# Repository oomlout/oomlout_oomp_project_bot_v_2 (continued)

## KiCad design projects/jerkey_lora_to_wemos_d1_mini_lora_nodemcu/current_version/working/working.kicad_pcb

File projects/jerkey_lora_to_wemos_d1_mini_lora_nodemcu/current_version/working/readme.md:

# lora_to_wemos_d1_mini
 
## summary 
* id: jerkey_lora_to_wemos_d1_mini_lora_nodemcu
* user: jerkey
* name: lora_to_wemos_d1_mini
* board: lora_nodemcu
* repo: https://github.com/jerkey/Lora-to-Wemos-D1-mini
* src_file_repo_kicad_pcb: lora_nodemcu.kicad_pcb
* src_file_repo_kicad_pcb_link: https://github.com/jerkey/Lora-to-Wemos-D1-mini/tree/master/lora_nodemcu.kicad_pcb

* src_file_repo_sch: lora_nodemcu.sch
* src_file_repo_sch_link: https://github.com/jerkey/Lora-to-Wemos-D1-mini/tree/master/lora_nodemcu.sch
* full details link: https://github.com/oomlout/oomlout_oomp_project_bot_v_2/tree/main/projects/jerkey_lora_to_wemos_d1_mini_lora_nodemcu/current_version/working

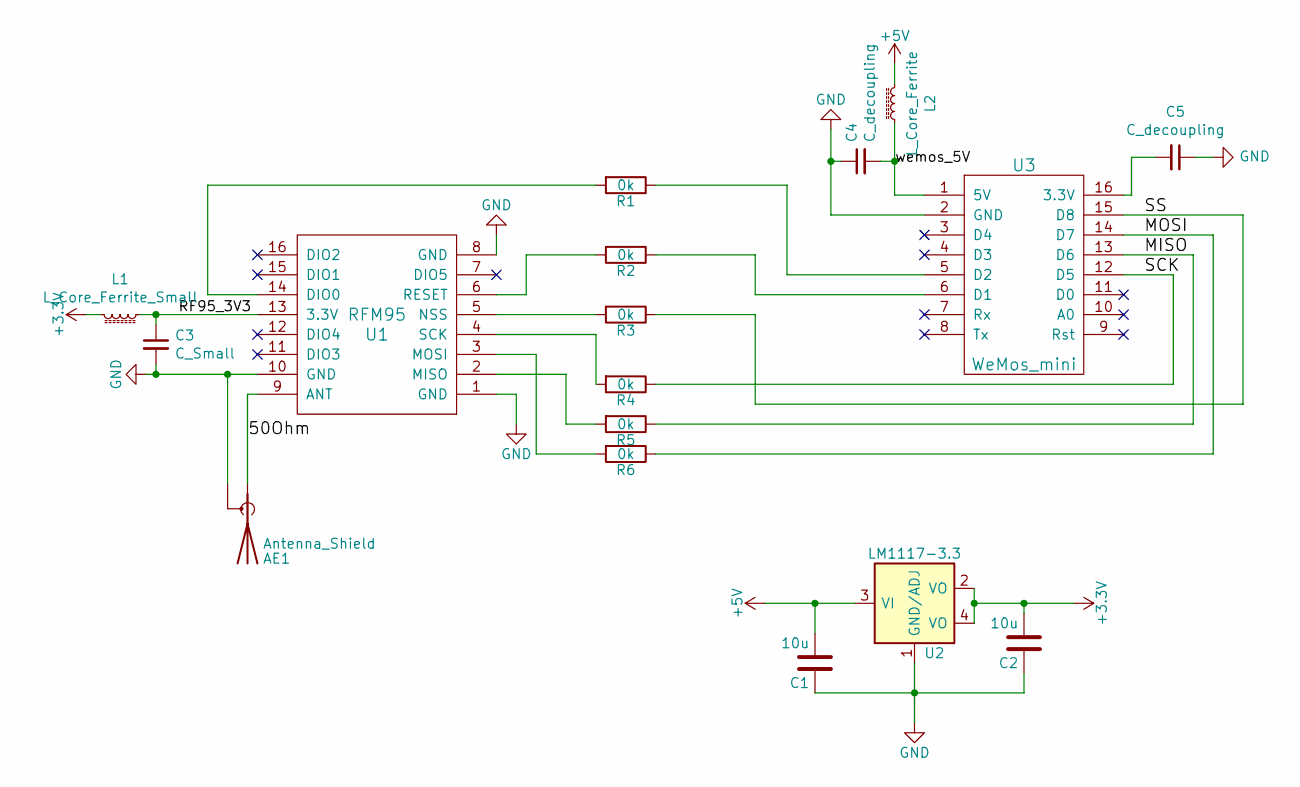
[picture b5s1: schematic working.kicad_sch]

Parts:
AE1: Antenna_Shield; Molex_SMA_Jack_Edge_Mount
C1, C2: 10u; C_0805_HandSoldering
C3: C_Small; C_0805_HandSoldering
C4, C5: C_decoupling; C_0805_HandSoldering
L1: L_Core_Ferrite_Small; L_0805_HandSoldering
L2: L_Core_Ferrite; L_0805_HandSoldering
R1, R2, R3, R4, R5, R6: 0k; R_0805_HandSoldering
U1: RFM95
U2: LM1117-3.3; SOT-223
U3: WeMos_mini; D1_mini_board

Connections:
+3V3: C2.2, L1.2, U2.2 (VO), U2.4 (VO)
+5V: C1.2, L2.2, U2.3 (VI)
/50Ohm: AE1.1 (A), U1.9 (ANT)
/MISO: R5.1, U3.13 (D6)
/MOSI: R6.1, U3.14 (D7)
/RF95_3V3: C3.1, L1.1, U1.13 (3.3V)
/SCK: R4.1, U3.12 (D5)
/SS: R3.1, U3.15 (D8)
/wemos_5V: C4.2, L2.1, U3.1 (5V)
GND: AE1.2 (Shield), C1.1, C2.1, C3.2, C4.1, C5.1, U1.1 (GND), U1.8 (GND), U1.10 (GND), U2.1 (GND/ADJ), U3.2 (GND)
unnamed: C5.2, U3.16 (3.3V)
unnamed: R1.1, U3.5 (D2)
unnamed: R1.2, U1.14 (DIO0)
unnamed: R2.1, U3.6 (D1)
unnamed: R2.2, U1.6 (RESET)
unnamed: R3.2, U1.5 (NSS)
unnamed: R4.2, U1.4 (SCK)
unnamed: R5.2, U1.2 (MISO)
unnamed: R6.2, U1.3 (MOSI)

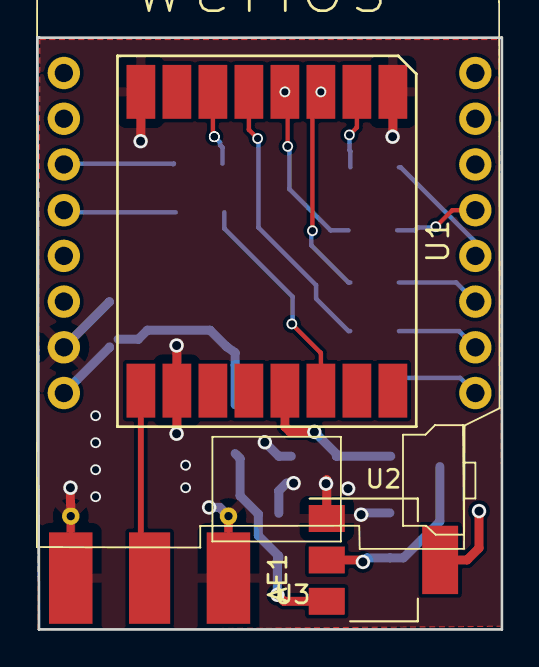
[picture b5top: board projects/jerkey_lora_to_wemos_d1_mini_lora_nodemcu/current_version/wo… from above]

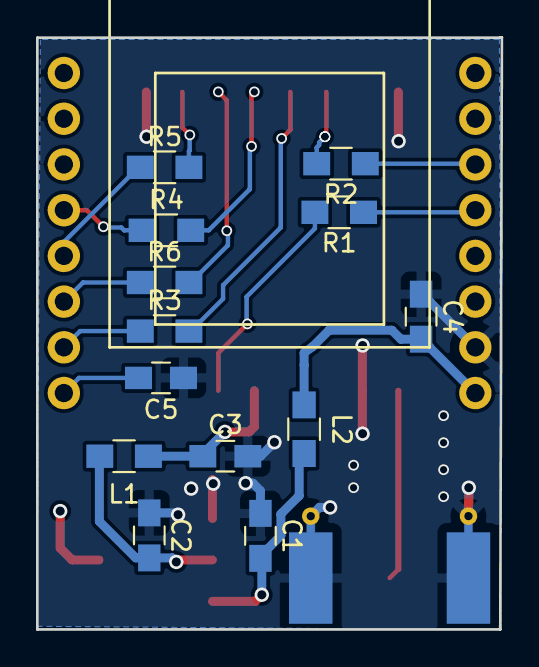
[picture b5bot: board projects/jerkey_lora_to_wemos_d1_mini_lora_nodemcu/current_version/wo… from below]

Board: 4 copper layers, 25.8 x 32.9 mm, 17 parts (13 on the bottom side), 19 nets.

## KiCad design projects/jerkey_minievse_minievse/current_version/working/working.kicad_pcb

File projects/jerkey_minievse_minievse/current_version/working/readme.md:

# minievse
 
## summary 
* id: jerkey_minievse_minievse
* user: jerkey
* name: minievse
* board: minievse
* repo: https://github.com/jerkey/minievse
* src_file_repo_kicad_pcb: minievse.kicad_pcb
* src_file_repo_kicad_pcb_link: https://github.com/jerkey/minievse/tree/master/minievse.kicad_pcb

* src_file_repo_sch: minievse.sch
* src_file_repo_sch_link: https://github.com/jerkey/minievse/tree/master/minievse.sch
* full details link: https://github.com/oomlout/oomlout_oomp_project_bot_v_2/tree/main/projects/jerkey_minievse_minievse/current_version/working

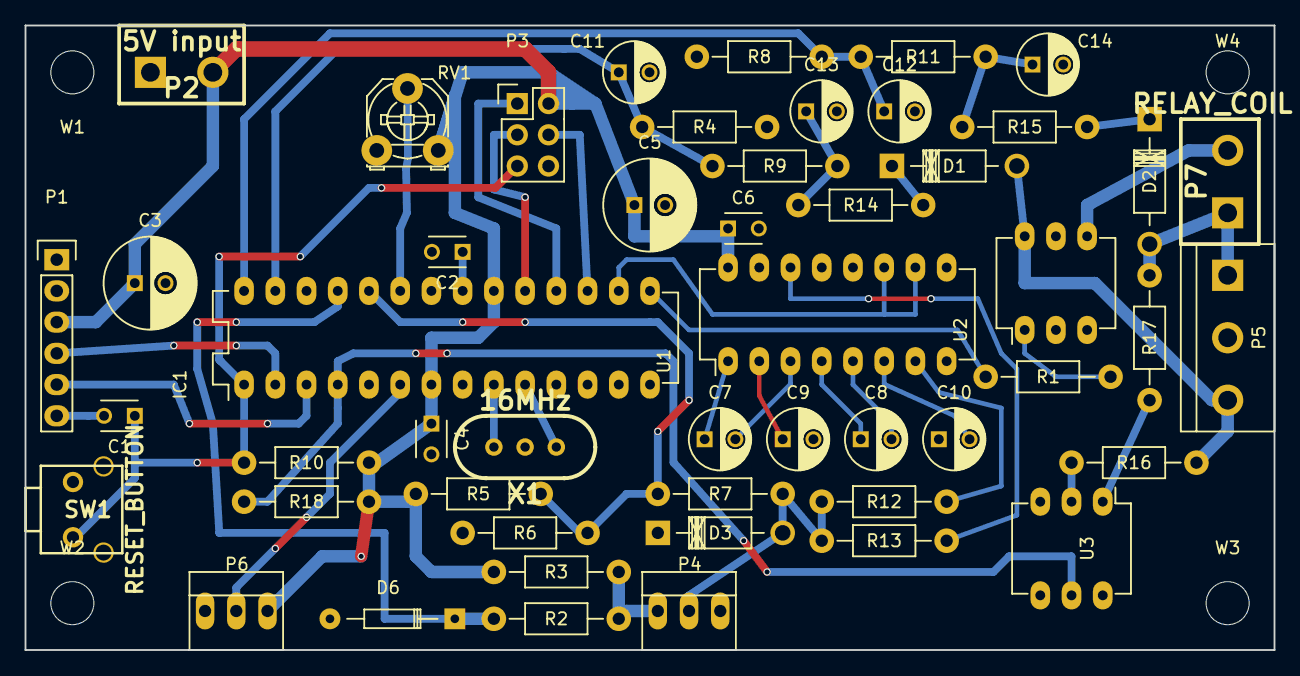
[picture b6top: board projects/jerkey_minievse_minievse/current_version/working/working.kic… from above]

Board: 2 copper layers, 101.6 x 50.8 mm, 54 parts (0 on the bottom side), 41 nets.

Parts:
C1, C2, C4, C6: 104; C_Disc_D3_P2.5
C3, C5: 100uF; C_Radial_D7.5_L11.2_P2.5
C7, C8, C9, C10: 1uF; C_Radial_D5_L6_P2.5
C11, C12, C13, C14: 10uF; C_Radial_D5_L6_P2.5
D1, D2: 1N4007; Diode_DO-41_SOD81_Horizontal_RM10_refdes_in_box
D3: P6KE16CA; Diode_DO-41_SOD81_Horizontal_RM10_refdes_in_box
D6: 1N4148; Diode_DO-35_SOD27_Horizontal_RM10
IC1: ATMEGA328P-P; DIP-28_W7.62mm_LongPads
P1: SERIAL; Pin_Header_Straight_1x06
P2: 5V input; CCFLHV
P3: ICSP; Pin_Header_Straight_2x03
P4: Pilot; PINHEAD1-3
P5: AC_GND_AC; bornier3
P6: LED_STRIP; PINHEAD1-3
P7: RELAY_COIL; CCFLHV
R1: 220; Resistor_Horizontal_RM10mm_refdes_in_box
R2, R10, R18: 10K; Resistor_Horizontal_RM10mm_refdes_in_box
R3: 1K; Resistor_Horizontal_RM10mm_refdes_in_box
R4, R8, R9, R11: 2550; Resistor_Horizontal_RM10mm_refdes_in_box
R5: 56K; Resistor_Horizontal_RM10mm_refdes_in_box
R6: 100K; Resistor_Horizontal_RM10mm_refdes_in_box
R7: 200K; Resistor_Horizontal_RM10mm_refdes_in_box
R12, R13: 1200; Resistor_Horizontal_RM10mm_refdes_in_box
R14, R15: 50K; Resistor_Horizontal_RM10mm_refdes_in_box
R16, R17: 15K; Resistor_Horizontal_RM10mm_refdes_in_box
RV1: POT; Potentiometer_Triwood_RM-065
SW1: RESET_BUTTON; SW-1825027-5
U1: MAX232; DIP-16_W7.62mm_LongPads
U2: MOC3021M; DIP-6_W7.62mm_LongPads
U3: H11AA; DIP-6_W7.62mm_LongPads
W1, W2, W3, W4: MountingHole_3.5mm
X1: 16MHz; HC-49V-OR-RESONATOR

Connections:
+5VD: C3.1, C4.1, C5.1, C6.1, IC1.7, IC1.20, P1.3, P2.2, P3.2, P6.3, R3.2, R5.1, R10.1, R18.1, RV1.3, U1.16
/AC_SENSE_1: C11.1, IC1.27, R4.1, R9.2
/AC_SENSE_2: C12.1, IC1.28, R8.1, R11.2
/AC_ZEROX: IC1.4, R18.2, U3.5
/AMP_KNOB: IC1.23, RV1.2
/LED_DATA: IC1.6, P6.2
/PILOT: D3.2, P4.2, R7.1, R12.1, R13.1
/PILOTREAD: IC1.24, R5.2, R6.1, R7.2
/PP: P4.1, R2.2, R3.1
/PP_READ: D6.1, IC1.25, R2.1
/PWM: IC1.16, U1.10, U1.11
/RELAY_TRIAC: IC1.15, R1.2
/RX: IC1.2, P1.4
/TX: IC1.3, P1.5
/miso: IC1.18, P3.1
/mosi: IC1.17, P3.4
/reset: C1.1, IC1.1, P3.5, R10.2, SW1.1
/sck: IC1.19, P3.3
GND: C2.2, C3.2, C4.2, C5.2, C6.2, C9.2, C10.1, C11.2, C12.2, C13.2, C14.2, D3.1, D6.2, IC1.8, IC1.22, P1.2, P2.1, P3.6, P4.3, P5.2, P6.1, R4.2, R6.2, R8.2, RV1.1, SW1.2, U1.15, U2.2, U3.4, X1.3
unnamed: C1.2, P1.6
unnamed: C2.1, IC1.21
unnamed: C7.1, U1.1
unnamed: C7.2, U1.3
unnamed: C8.1, U1.4
unnamed: C8.2, U1.5
unnamed: C9.1, U1.2
unnamed: C10.2, U1.6
unnamed: C13.1, R9.1, R14.1
unnamed: C14.1, R11.1, R15.1
unnamed: D2.2, P5.1, P7.1, R17.2
unnamed: D1.1, R14.2
unnamed: D1.2, P5.3, R16.2, U2.6
unnamed: D2.1, R15.2
unnamed: IC1.9, X1.2
unnamed: IC1.10, X1.1
unnamed: P7.2, U2.4
unnamed: R1.1, U2.1
unnamed: R12.2, U1.7
unnamed: R13.2, U1.14
unnamed: R16.1, U3.2
unnamed: R17.1, U3.1
